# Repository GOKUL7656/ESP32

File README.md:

# ESP32
ESP32 microcontroller with USB protocols

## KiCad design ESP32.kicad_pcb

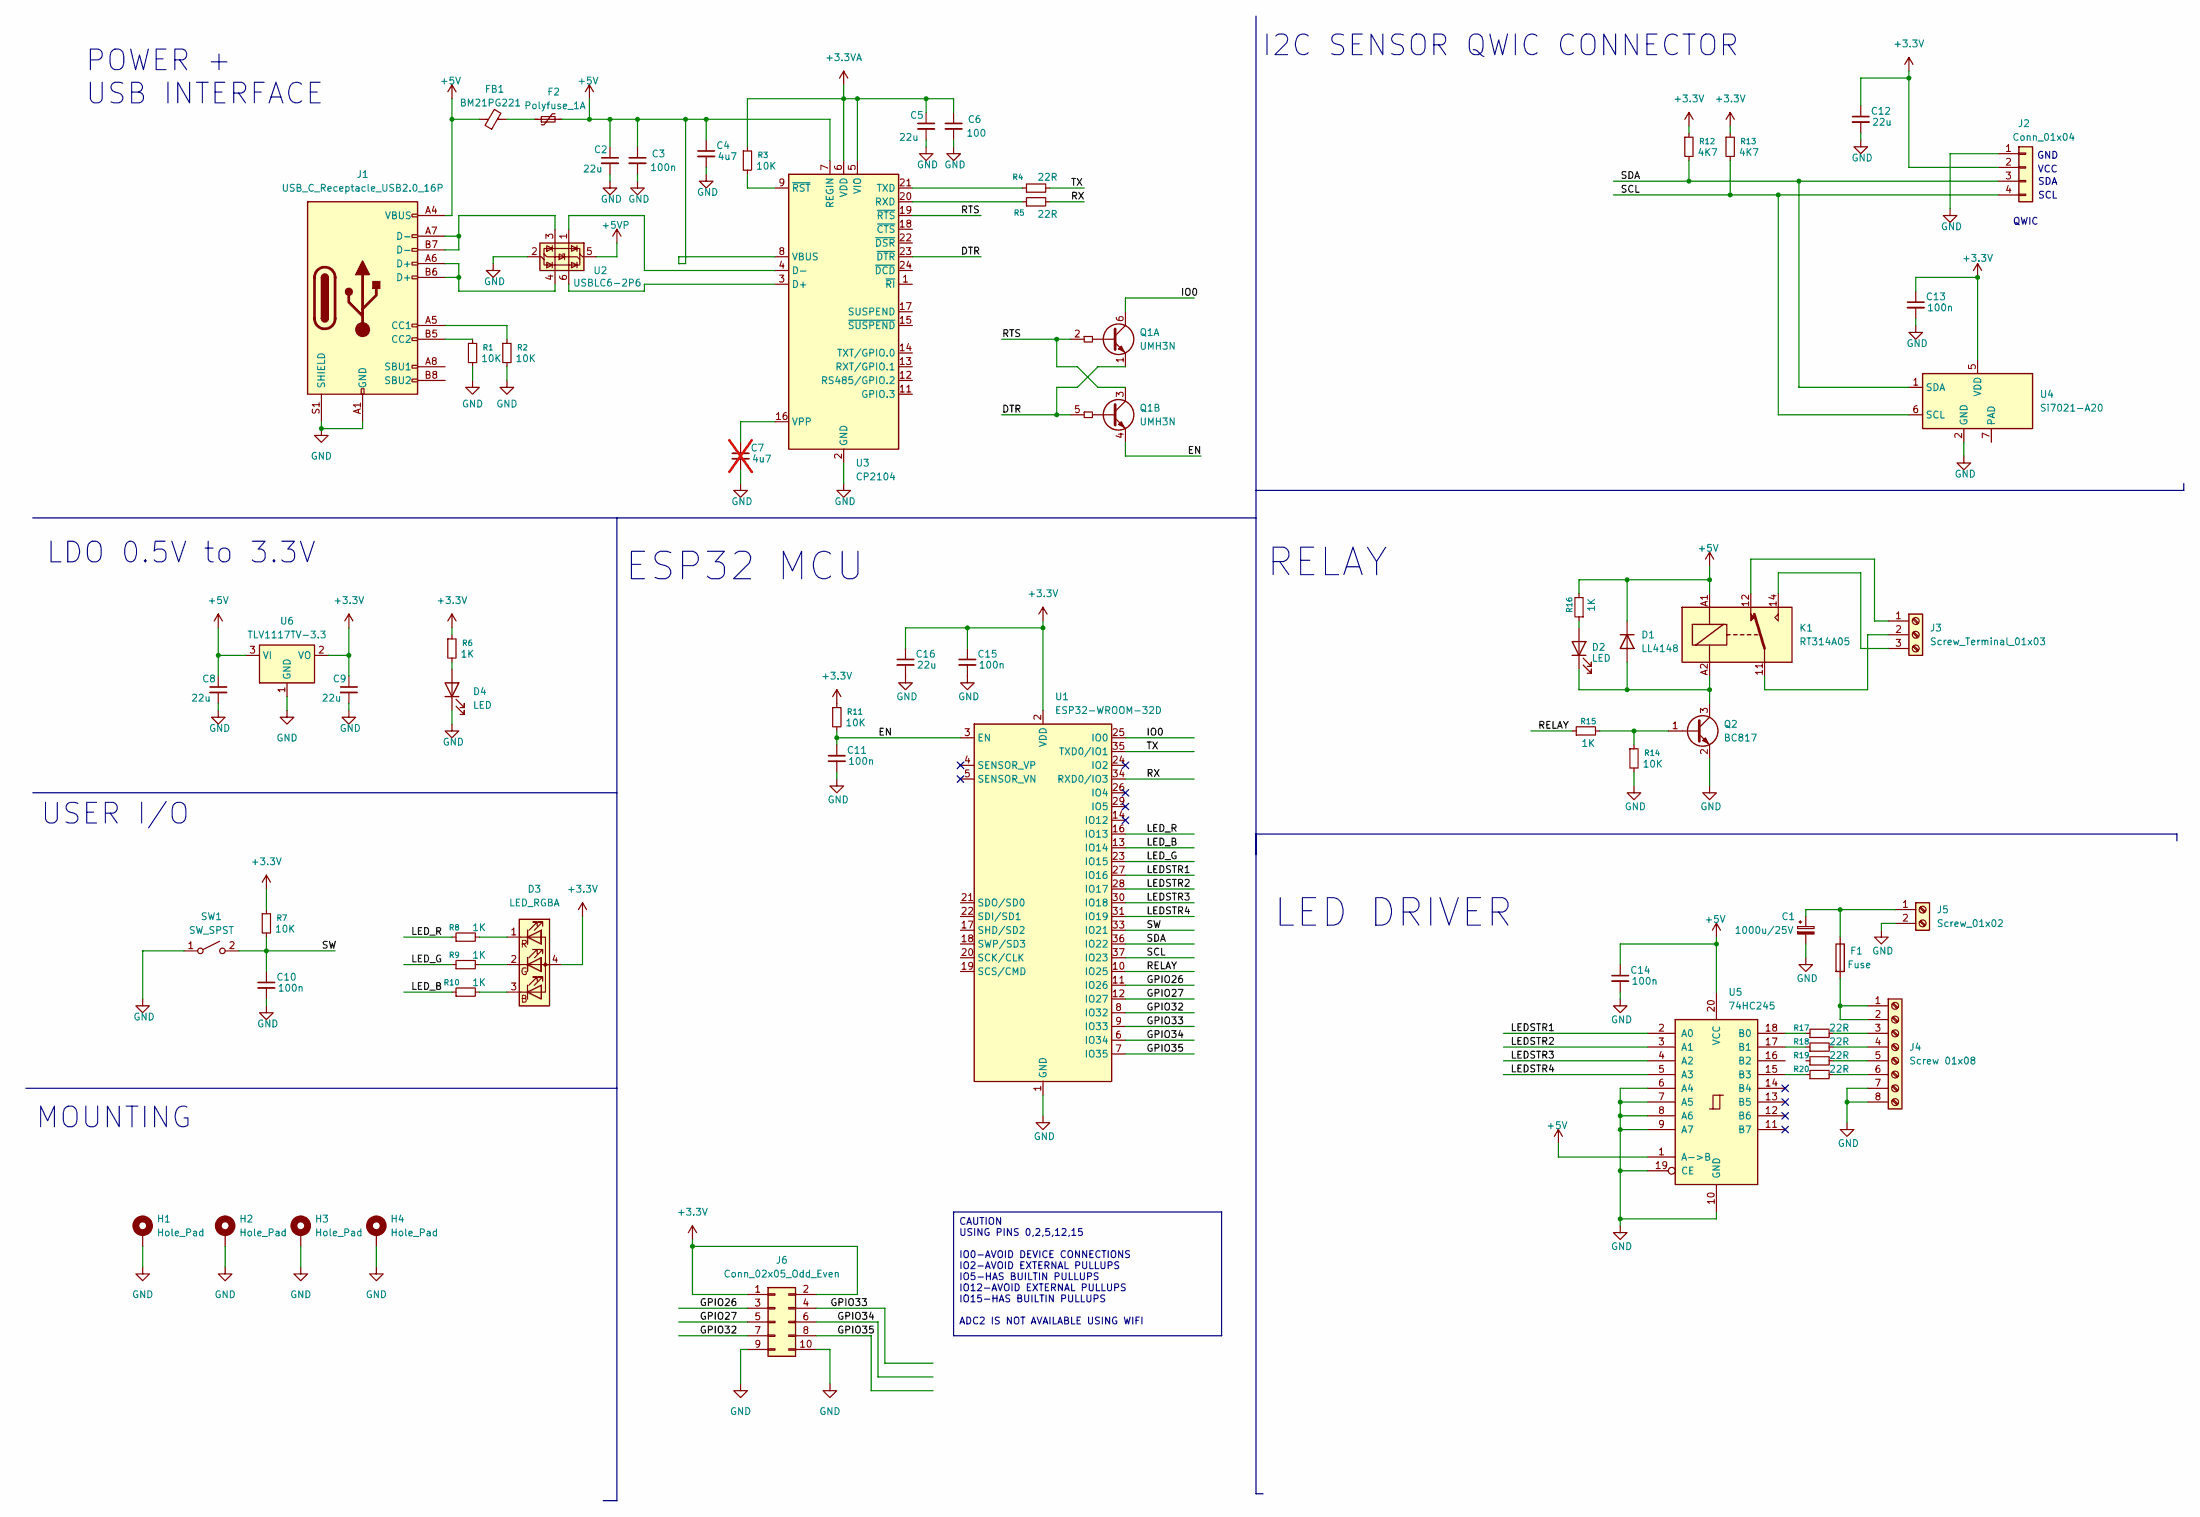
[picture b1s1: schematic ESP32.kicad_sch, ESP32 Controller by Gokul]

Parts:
C1: 1000u/25V; C_0201_0603Metric
C2, C5, C8, C9, C12, C16: 22u; C_0805_2012Metric
C3, C10, C11, C13, C14, C15: 100n; C_0805_2012Metric
C4: 4u7; C_0201_0603Metric
C6: 100; C_0201_0603Metric
C7: 4u7; C_0201_0603Metric; not fitted
D1: LL4148; D_MiniMELF
D2, D4: LED; D_MiniMELF
D3: LED_RGBA; LED_RGB_5050-6
F1: Fuse; Fuse_0603_1608Metric
F2: Polyfuse_1A; Fuse_0805_2012Metric
FB1: BM21PG221; L_0805_2012Metric
H1, H2, H3, H4: Hole_Pad; PinHeader_1x01_P1.00mm_Vertical
J1: USB_C_Receptacle_USB2.0_16P; USB_C_Receptacle_GCT_USB4115-03-C
J2: Conn_01x04; PinHeader_1x04_P1.00mm_Horizontal
J3: Screw_Terminal_01x03; TerminalBlock_Phoenix_MKDS-3-3-5.08_1x03_P5.08mm_Horizontal
J4: Screw 01x08; TerminalBlock_Phoenix_MKDS-3-8-5.08_1x08_P5.08mm_Horizontal
J5: Screw_01x02; TerminalBlock_Phoenix_MKDS-3-2-5.08_1x02_P5.08mm_Horizontal
J6: Conn_02x05_Odd_Even; PinHeader_2x05_P1.00mm_Horizontal
K1: RT314A05; Relay_SPDT_Schrack-RT1-16A-FormC_RM5mm
Q1: UMH3N; SOT-363_SC-70-6
Q2: BC817; SOT-23
R1, R2, R3, R7, R11, R14: 10K; R_0201_0603Metric
R4, R5, R17, R18, R19, R20: 22R; R_0201_0603Metric
R6, R8, R9, R10, R15, R16: 1K; R_0201_0603Metric
R12, R13: 4K7; R_0201_0603Metric
SW1: SW_SPST; SW_PUSH_6mm_H8mm
U1: ESP32-WROOM-32D
U2: USBLC6-2P6; SOT-666
U3: CP2104; QFN-24-1EP_4x4mm_P0.5mm_EP2.6x2.6mm
U4: Si7021-A20; DFN-6-1EP_3x3mm_P1mm_EP1.5x2.4mm
U5: 74HC245; SSOP-20_3.9x8.7mm_P0.635mm
U6: TLV1117TV-3.3; SOT-223-3_TabPin2

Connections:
+3.3V: C9.1, C12.1, C13.1, C15.1, C16.1, D3.4 (A), J2.2, J6.1, J6.2, R6.1, R7.1, R11.1, R12.1, R13.1, U1.2 (VDD), U4.5 (VDD), U6.2 (VO)
+3.3VA: C5.1, C6.1, R3.1, U3.5 (VIO), U3.6 (VDD)
+5V: C2.1, C3.1, C4.1, C8.1, C14.1, D1.1 (K), F2.2, FB1.1, J1.A4 (VBUS), J1.A9 (VBUS), J1.B4 (VBUS), J1.B9 (VBUS), K1.A1, R16.2, U3.7 (REGIN), U3.8 (VBUS), U5.1 (A->B), U5.20 (VCC), U6.3 (VI)
+5VP: U2.5 (VBUS)
/DTR: Q1.1 (E1), Q1.5 (B2), U3.23 (~DTR)
/EN: C11.1, Q1.4 (E2), R11.2, U1.3 (EN)
/GPIO26: J6.3, U1.11 (IO26)
/GPIO27: J6.5, U1.12 (IO27)
/GPIO32: J6.7, U1.8 (IO32)
/GPIO33: J6.4, U1.9 (IO33)
/GPIO34: J6.6, U1.6 (IO34)
/GPIO35: J6.8, U1.7 (IO35)
/IO0: Q1.6 (C1), U1.25 (IO0)
/LEDSTR1: U1.27 (IO16), U5.2 (A0)
/LEDSTR2: U1.28 (IO17), U5.3 (A1)
/LEDSTR3: U1.30 (IO18), U5.4 (A2)
/LEDSTR4: U1.31 (IO19), U5.5 (A3)
/LED_B: R10.1, U1.13 (IO14)
/LED_G: R9.1, U1.23 (IO15)
/LED_R: R8.1, U1.16 (IO13)
/RELAY: R15.1, U1.10 (IO25)
/RTS: Q1.2 (B1), Q1.3 (C2), U3.19 (~RTS)
/RX: R5.2, U1.34 (RXD0/IO3)
/SCL: J2.4, R13.2, U1.37 (IO23), U4.6 (SCL)
/SDA: J2.3, R12.2, U1.36 (IO22), U4.1 (SDA)
/SW: C10.1, R7.2, SW1.2 (B), U1.33 (IO21)
/TX: R4.2, U1.35 (TXD0/IO1)
GND: C1.2, C2.2, C3.2, C4.2, C5.2, C6.2, C7.2, C8.2, C9.2, C10.2, C11.2, C12.2, C13.2, C14.2, C15.2, C16.2, D4.1 (K), H1.1, H2.1, H3.1, H4.1, J1.A1 (GND), J1.A12 (GND), J1.B1 (GND), J1.B12 (GND), J1.S1 (SHIELD), J2.1, J4.7, J4.8, J5.2, J6.9, J6.10, Q2.2 (E), R1.2, R2.2, R14.2, SW1.1 (A), U1.1 (GND), U1.15 (GND), U1.38 (GND), U1.39 (GND), U2.2 (GND), U3.2 (GND), U3.25 (GND), U4.2 (GND), U5.6 (A4), U5.7 (A5), U5.8 (A6), U5.9 (A7), U5.10 (GND), U5.19 (CE), U6.1 (GND)
unnamed: D1.2 (A), D2.1 (K), K1.A2, Q2.3 (C)
unnamed: D2.2 (A), R16.1
unnamed: D3.3 (BK), R10.2
unnamed: D3.2 (GK), R9.2
unnamed: D3.1 (RK), R8.2
unnamed: D4.2 (A), R6.2
unnamed: F2.1, FB1.2
unnamed: J1.A5 (CC1), R2.1
unnamed: J1.B5 (CC2), R1.1
unnamed: J1.A6 (D+), J1.B6 (D+), U2.4 (I/O2)
unnamed: J1.A7 (D-), J1.B7 (D-), U2.3 (I/O2)
unnamed: J3.1, K1.12
unnamed: J3.2, K1.11
unnamed: J3.3, K1.14
unnamed: F1.2, J4.1, J4.2
unnamed: J4.3, R17.2
unnamed: J4.4, R18.2
unnamed: J4.5, R19.2
unnamed: J4.6, R20.2
unnamed: C1.1, F1.1, J5.1
unnamed: Q2.1 (B), R14.1, R15.2
unnamed: U2.6 (I/O1), U3.3 (D+)
unnamed: U2.1 (I/O1), U3.4 (D-)
unnamed: R5.1, U3.20 (RXD)
unnamed: R4.1, U3.21 (TXD)
unnamed: C7.1, U3.16 (VPP)
unnamed: R3.2, U3.9 (~RST)
unnamed: R17.1, U5.18 (B0)
unnamed: R18.1, U5.17 (B1)
unnamed: R20.1, U5.15 (B3)

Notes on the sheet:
POWER + USB INTERFACE
LED DRIVER
GND
LDO 0.5V to 3.3V
MOUNTING
USER I/O
VCC
I2C SENSOR QWIC CONNECTOR
ESP32 MCU
SDA
QWIC
SCL
RELAY
CAUTION USING PINS 0,2,5,12,15 IO0-AVOID DEVICE CONNECTIONS IO2-AVOID EXTERNAL PULLUPS IO5-HAS BUILTIN PULLUPS IO12-AVOID EXTERNAL PULLUPS IO15-HAS BUILTIN PULLUPS ADC2 IS NOT AVAILABLE USING WIFI

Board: 2 copper layers, 63 parts (0 on the bottom side), 57 nets, no tracks yet.
